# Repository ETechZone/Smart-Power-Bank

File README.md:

# Smart-Power-Bank
my current project in reewo

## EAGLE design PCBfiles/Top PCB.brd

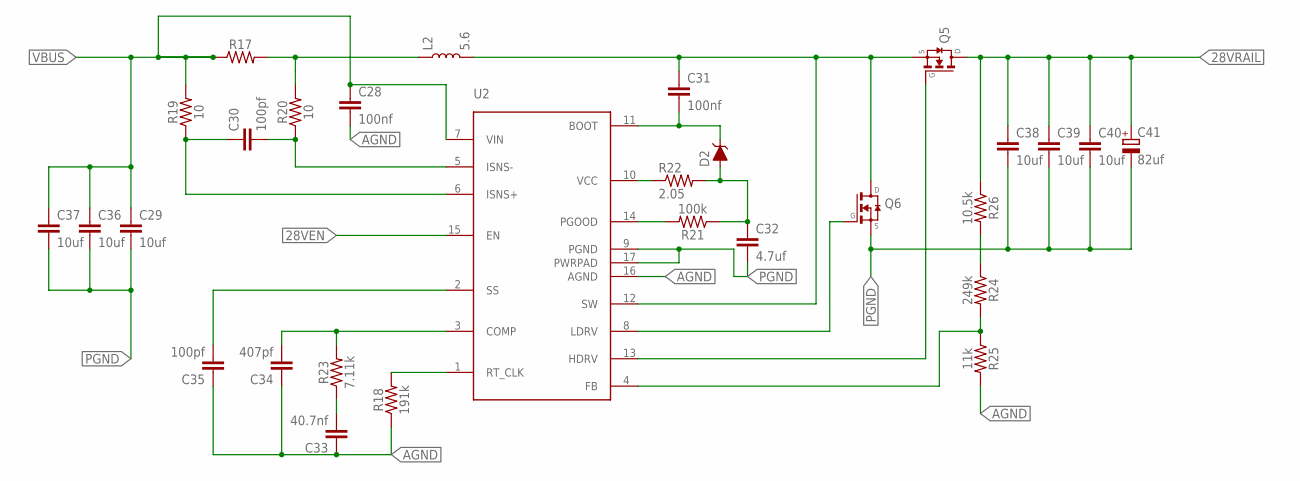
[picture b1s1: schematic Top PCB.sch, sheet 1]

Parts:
C28, C31: 100nf; C0402K
C29, C36, C37, C38, C39, C40: 10uf; C0805K
C30, C35: 100pf; C0402K
C32: 4.7uf; C0402K
C33: 40.7nf; C0402K
C34: 407pf; C0402K
C41: 82uf; CAPAE830X1040
D2: SS24FL; SODFL3617X108
L2: 5.6; RESM7275X700
Q5, Q6: SIS184DN-T1-GE3
R17: LRMAM2512-R0035FT4; RESC6432X90
R18: 191k; 0402
R19, R20: 10; 0402
R21: 100k; 0402
R22: 2.05; R0603
R23: 7.11k; 0402
R24: 249k; 0402
R25: 11k; 0402
R26: 10.5k; 0402
U2: TPS43061; QFN50P300X300X100-17T80X120

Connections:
28VEN: U2.15 (EN)
28VRAIL: C38.1, C39.1, C40.1, C41.1 (+), Q5.P$5 (D), Q5.P$6 (D), Q5.P$7 (D), Q5.P$8 (D), Q5.P$9 (D), R26.1; also elsewhere on the board
AGND: C28.2, C33.1, C34.1, C35.1, R18.1, R25.2, U2.16 (AGND)
unnamed: C31.1, L2.2, Q5.P$1 (S), Q5.P$2 (S), Q5.P$3 (S), Q6.P$5 (D), Q6.P$6 (D), Q6.P$7 (D), Q6.P$8 (D), Q6.P$9 (D), U2.12 (SW)
unnamed: R24.1, R26.2
unnamed: L2.1, R17.2, R20.2
unnamed: C30.1, R19.1, U2.6 (ISNS+)
unnamed: C30.2, R20.1, U2.5 (ISNS-)
unnamed: C31.2, D2.1 (C), U2.11 (BOOT)
unnamed: C32.1, D2.2 (A), R21.1, R22.2
unnamed: R21.2, U2.14 (PGOOD)
unnamed: R22.1, U2.10 (VCC)
unnamed: R18.2, U2.1 (RT_CLK)
unnamed: Q5.P$4 (G), U2.13 (HDRV)
unnamed: Q6.P$4 (G), U2.8 (LDRV)
unnamed: R24.2, R25.1, U2.4 (FB)
unnamed: C34.2, R23.2, U2.3 (COMP)
unnamed: C33.2, R23.1
unnamed: C35.2, U2.2 (SS)
PGND: C29.2, C32.2, C36.2, C37.2, C38.2, C39.2, C40.2, C41.2 (-), Q6.P$1 (S), Q6.P$2 (S), Q6.P$3 (S), U2.9 (PGND), U2.17 (PWRPAD); also elsewhere on the board
VBUS: C28.1, C29.1, C36.1, C37.1, R17.1, R19.2, U2.7 (VIN)

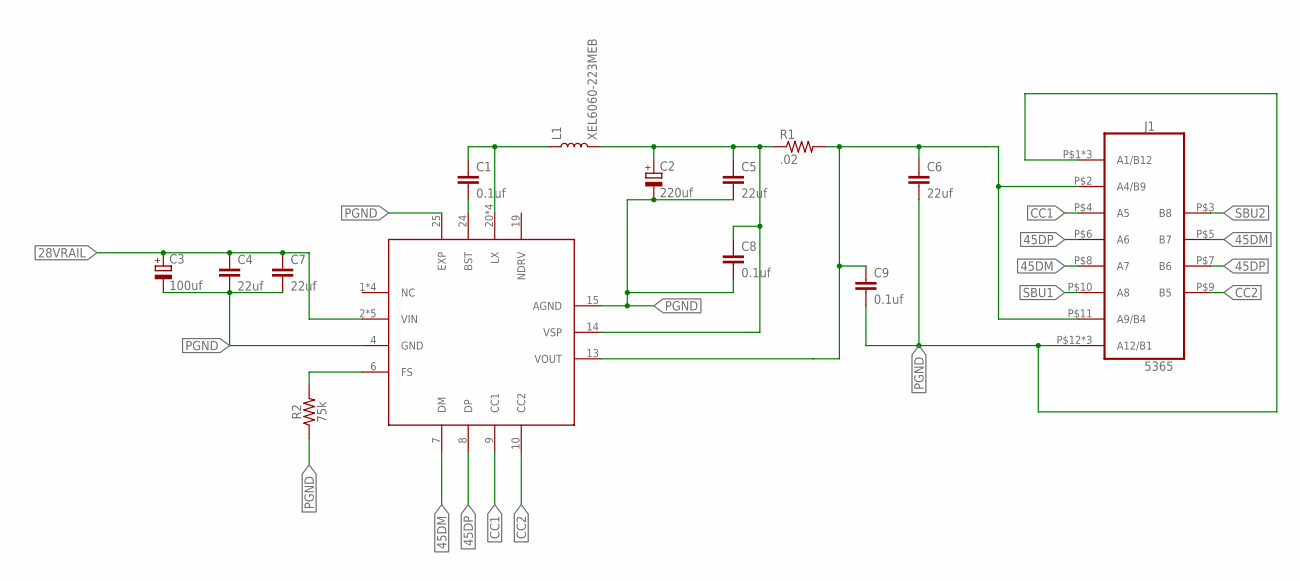
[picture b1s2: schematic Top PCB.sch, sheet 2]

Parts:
C1, C8, C9: 0.1uf; C0805K
C2: 220uf; CAPAE830X1040
C3: 100uf; CAPAE830X1040
C4, C5, C6, C7: 22uf; C0805K
J1: 5365
L1: XEL6060-223MEB; RESM6365X610
R1: .02; R0805
R2: 75k; 0402
U1: IP6518; QFN50P400X400X80-25T250

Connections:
28VRAIL: C3.1 (+), C4.1, C7.1, U1.2 (VIN), U1.3 (VIN), U1.16 (VIN), U1.17 (VIN), U1.18 (VIN); also elsewhere on the board
45DM: J1.P$5 (B7), J1.P$8 (A7), U1.7 (DM)
45DP: J1.P$6 (A6), J1.P$7 (B6), U1.8 (DP)
CC1: J1.P$4 (A5), U1.9 (CC1)
CC2: J1.P$9 (B5), U1.10 (CC2)
unnamed: C1.1, L1.1, U1.20 (LX), U1.21 (LX), U1.22 (LX), U1.23 (LX)
unnamed: C1.2, U1.24 (BST)
unnamed: C2.1 (+), C5.1, C8.1, L1.2, R1.1, U1.14 (VSP)
unnamed: C6.1, C9.1, J1.P$2 (A4/B9), J1.P$11 (A9/B4), R1.2, U1.13 (VOUT)
unnamed: R2.2, U1.6 (FS)
PGND: C2.2 (-), C3.2 (-), C4.2, C5.2, C6.2, C7.2, C8.2, C9.2, J1.P$1 (A1/B12), J1.P$12 (A12/B1), J1.P$13 (A1/B12), J1.P$14 (A12/B1), J1.P$15 (A1/B12), J1.P$16 (A12/B1), R2.1, U1.4 (GND), U1.15 (AGND), U1.25 (EXP); also elsewhere on the board
SBU1: J1.P$10 (A8)
SBU2: J1.P$3 (B8)

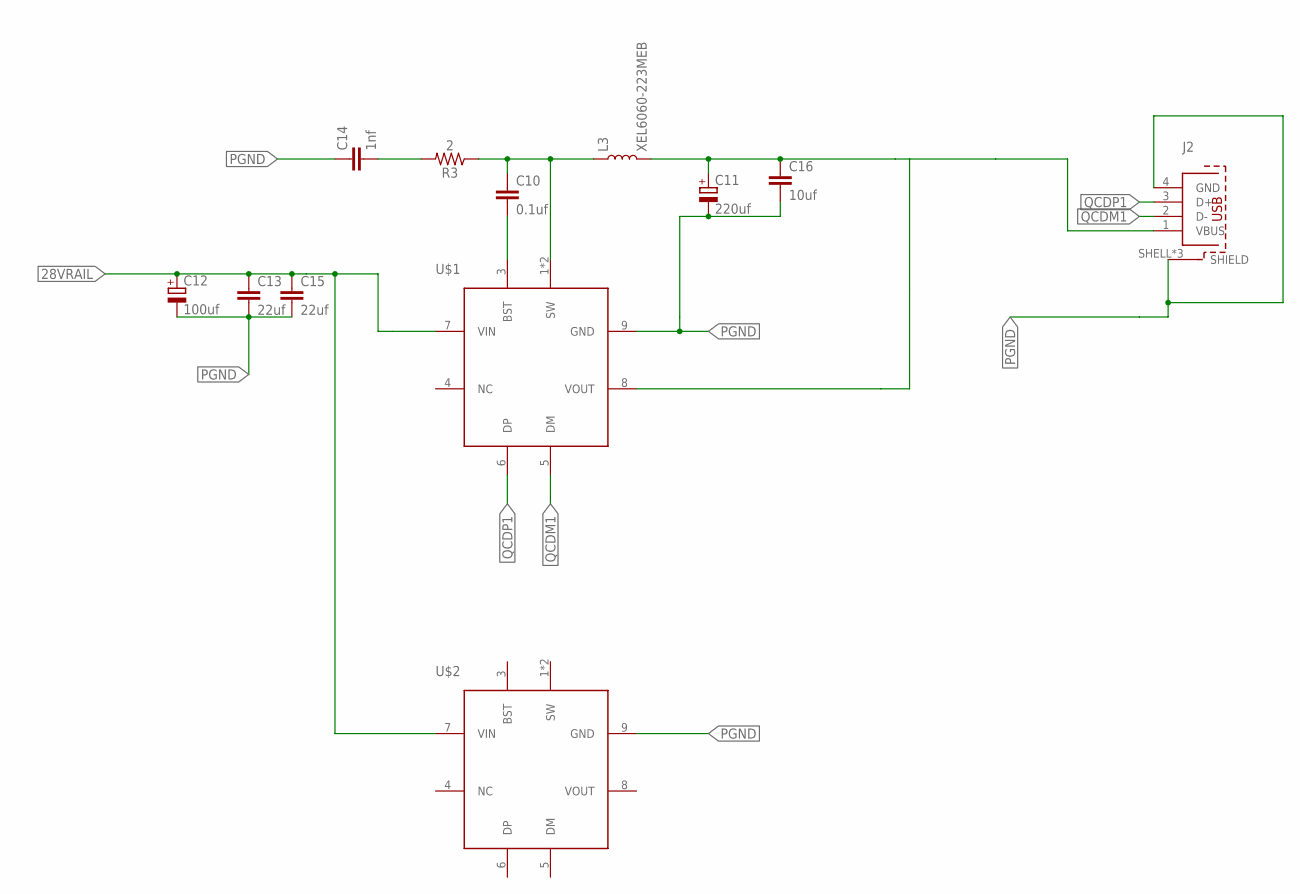
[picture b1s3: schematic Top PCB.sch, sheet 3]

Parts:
C10: 0.1uf; C0805K
C11: 220uf; CAPAE830X1040
C12: 100uf; CAPAE830X1040
C13, C15: 22uf; C0805K
C14: 1nf; C0402K
C16: 10uf; C0805K
J2: 614004184726
L3: XEL6060-223MEB; RESM6365X610
R3: 2; 0402
U$1, U$2: IP6505; SOIC127P600X165-9T209

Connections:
28VRAIL: C12.1 (+), C13.1, C15.1, U$1.7 (VIN), U$2.7 (VIN); also elsewhere on the board
unnamed: C10.1, L3.1, R3.1, U$1.1 (SW), U$1.2 (SW)
unnamed: C10.2, U$1.3 (BST)
unnamed: C14.2, R3.2
unnamed: J2.1 (VBUS), U$1.8 (VOUT)
unnamed: C11.1 (+), C16.1, L3.2
PGND: C11.2 (-), C12.2 (-), C13.2, C14.1, C15.2, C16.2, J2.4 (GND), J2.SHELL (SHIELD), J2.SHELL1 (SHIELD), J2.SHELL2 (SHIELD), U$1.9 (GND), U$2.9 (GND); also elsewhere on the board
QCDM1: J2.2 (D-), U$1.5 (DM)
QCDP1: J2.3 (D+), U$1.6 (DP)

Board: 2 copper layers, 55 parts (0 on the bottom side), 36 nets, no tracks yet.

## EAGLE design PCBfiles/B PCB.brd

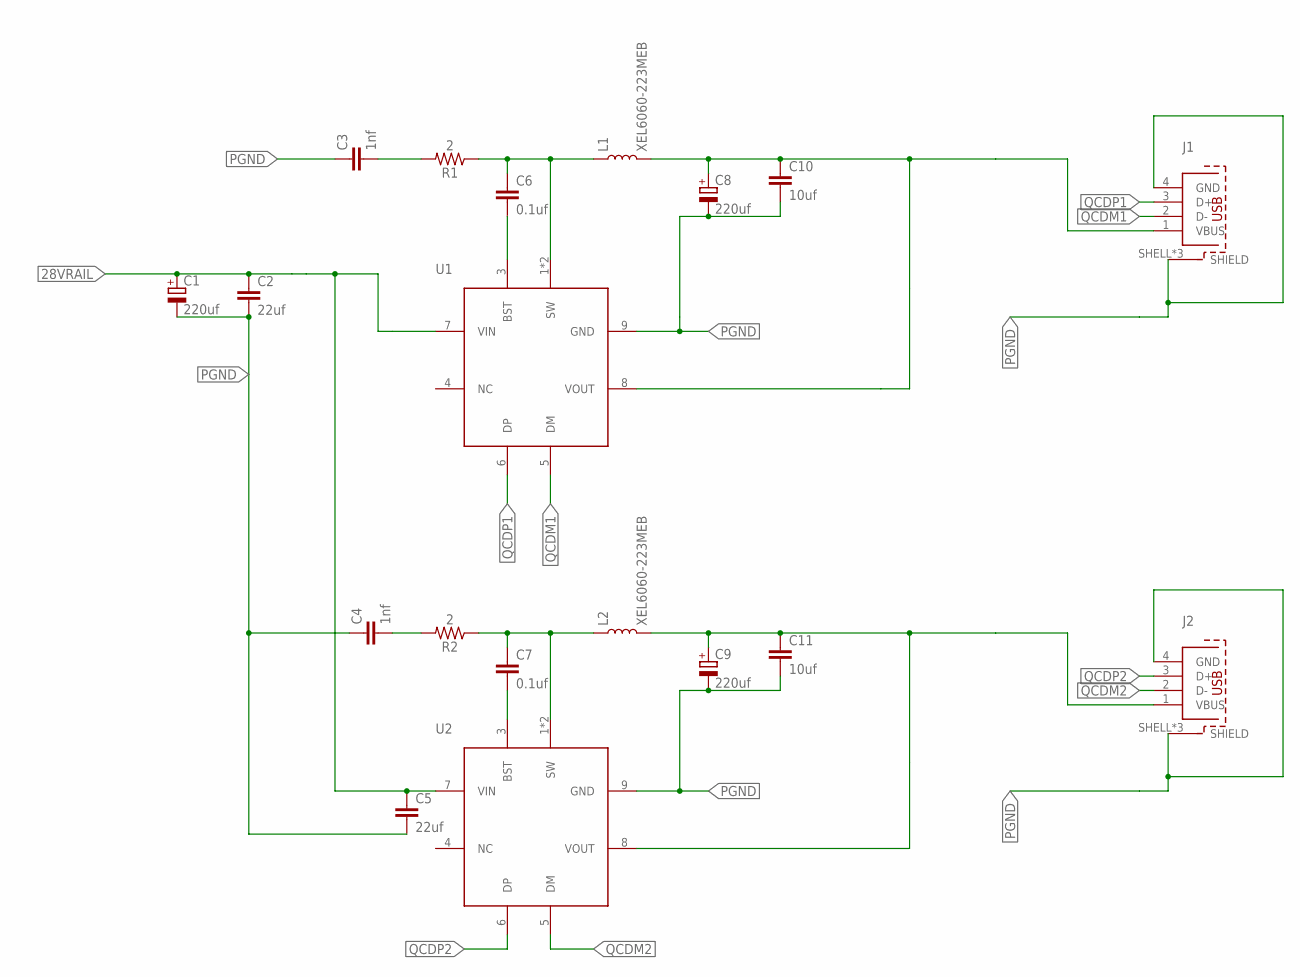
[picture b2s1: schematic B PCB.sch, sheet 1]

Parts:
C1: 220uf; CAPAE830X1040
C2, C5: 22uf; C0805K
C3, C4: 1nf; C0402K
C6, C7: 0.1uf; C0805K
C8, C9: 220uf; CAPAE660X800
C10, C11: 10uf; C0805K
J1, J2: 614004184726
L1, L2: XEL6060-223MEB; RESM6365X610
R1, R2: 2; 0402
U1, U2: IP6505; SOIC127P600X165-9T209

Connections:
28VRAIL: C1.1 (+), C2.1, C5.1, U1.7 (VIN), U2.7 (VIN); also elsewhere on the board
unnamed: C7.1, L2.1, R2.1, U2.1 (SW), U2.2 (SW)
unnamed: C7.2, U2.3 (BST)
unnamed: C6.1, L1.1, R1.1, U1.1 (SW), U1.2 (SW)
unnamed: C9.1 (+), C11.1, J2.1 (VBUS), L2.2, U2.8 (VOUT)
unnamed: C4.2, R2.2
unnamed: C6.2, U1.3 (BST)
unnamed: C3.2, R1.2
unnamed: C8.1 (+), C10.1, J1.1 (VBUS), L1.2, U1.8 (VOUT)
PGND: C1.2 (-), C2.2, C3.1, C4.1, C5.2, C8.2 (-), C9.2 (-), C10.2, C11.2, J1.4 (GND), J1.SHELL (SHIELD), J1.SHELL1 (SHIELD), J1.SHELL2 (SHIELD), J2.4 (GND), J2.SHELL (SHIELD), J2.SHELL1 (SHIELD), J2.SHELL2 (SHIELD), U1.9 (GND), U2.9 (GND); also elsewhere on the board
QCDM1: J1.2 (D-), U1.5 (DM)
QCDM2: J2.2 (D-), U2.5 (DM)
QCDP1: J1.3 (D+), U1.6 (DP)
QCDP2: J2.3 (D+), U2.6 (DP)

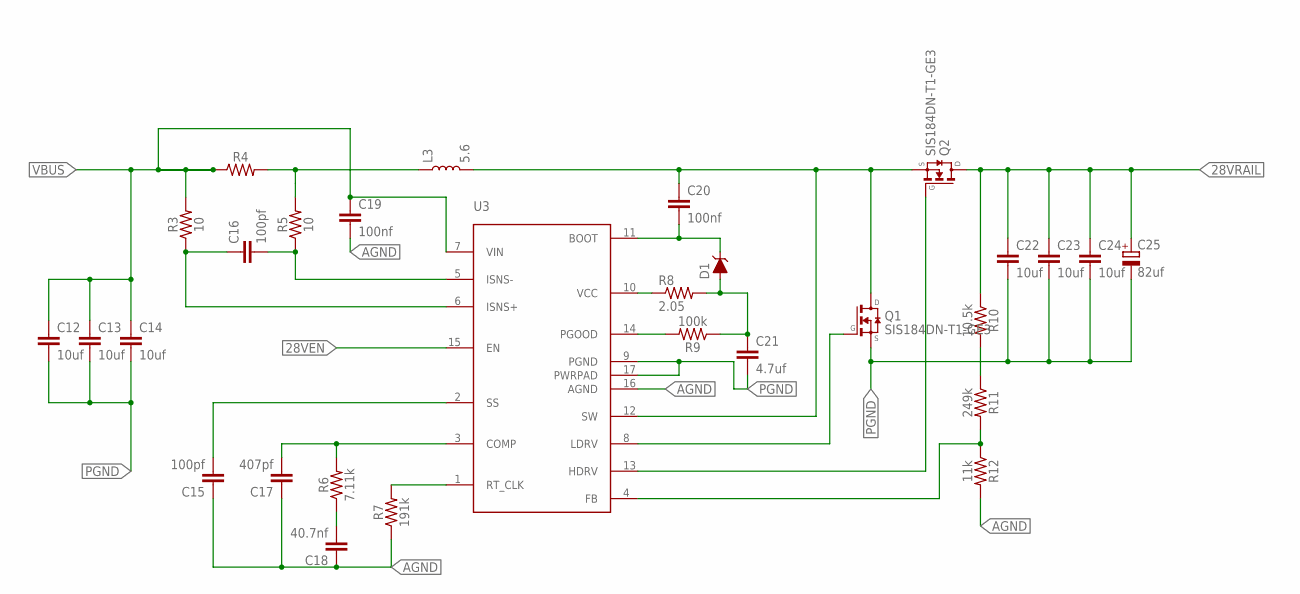
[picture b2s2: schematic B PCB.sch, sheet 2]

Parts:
C12, C13, C14, C22, C23, C24: 10uf; C0805K
C15, C16: 100pf; C0402K
C17: 407pf; C0402K
C18: 40.7nf; C0402K
C19, C20: 100nf; C0402K
C21: 4.7uf; C0402K
C25: 82uf; CAPAE660X800
D1: SS24FL; SODFL3617X108
L3: 5.6; RESM7275X700
Q1, Q2: SIS184DN-T1-GE3
R3, R5: 10; 0402
R4: LRMAM2512-R0035FT4; RESC6432X90
R6: 7.11k; 0402
R7: 191k; 0402
R8: 2.05; R0603
R9: 100k; 0402
R10: 10.5k; 0402
R11: 249k; 0402
R12: 11k; 0402
U3: TPS43061; QFN50P300X300X100-17T80X120

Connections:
28VEN: U3.15 (EN)
28VRAIL: C22.1, C23.1, C24.1, C25.1 (+), Q2.P$5 (D), Q2.P$6 (D), Q2.P$7 (D), Q2.P$8 (D), Q2.P$9 (D), R10.1; also elsewhere on the board
AGND: C15.1, C17.1, C18.1, C19.2, R7.1, R12.2, U3.16 (AGND)
unnamed: C20.1, L3.2, Q1.P$5 (D), Q1.P$6 (D), Q1.P$7 (D), Q1.P$8 (D), Q1.P$9 (D), Q2.P$1 (S), Q2.P$2 (S), Q2.P$3 (S), U3.12 (SW)
unnamed: R10.2, R11.1
unnamed: L3.1, R4.2, R5.2
unnamed: C16.1, R3.1, U3.6 (ISNS+)
unnamed: C16.2, R5.1, U3.5 (ISNS-)
unnamed: C20.2, D1.1 (C), U3.11 (BOOT)
unnamed: C21.1, D1.2 (A), R8.2, R9.1
unnamed: R9.2, U3.14 (PGOOD)
unnamed: R8.1, U3.10 (VCC)
unnamed: R7.2, U3.1 (RT_CLK)
unnamed: Q2.P$4 (G), U3.13 (HDRV)
unnamed: Q1.P$4 (G), U3.8 (LDRV)
unnamed: R11.2, R12.1, U3.4 (FB)
unnamed: C17.2, R6.2, U3.3 (COMP)
unnamed: C18.2, R6.1
unnamed: C15.2, U3.2 (SS)
PGND: C12.2, C13.2, C14.2, C21.2, C22.2, C23.2, C24.2, C25.2 (-), Q1.P$1 (S), Q1.P$2 (S), Q1.P$3 (S), U3.9 (PGND), U3.17 (PWRPAD); also elsewhere on the board
VBUS: C12.1, C13.1, C14.1, C19.1, R3.2, R4.1, U3.7 (VIN)

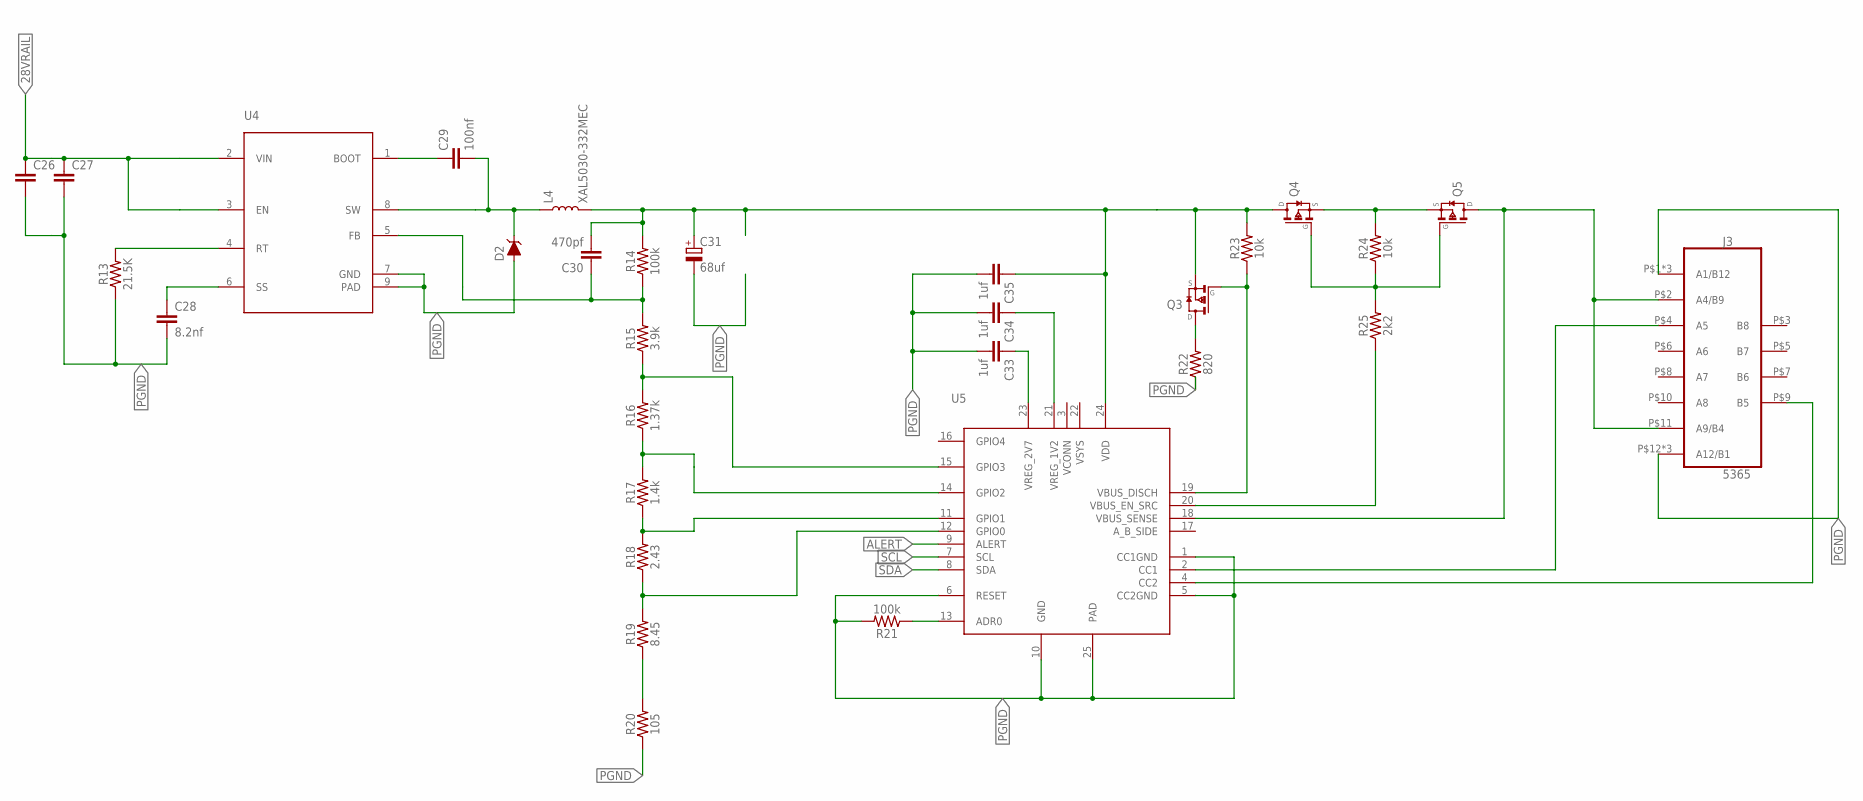
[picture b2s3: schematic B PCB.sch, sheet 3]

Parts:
C26, C27: C-EUC1210; C1210
C28: 8.2nf; C0402K
C29: 100nf; C0402K
C30: 470pf; C0402K
C31: 68uf; CAPAE830X1040
C33, C34, C35: 1uf; C0402K
D2: B560C-13-F; DIOM6859X250
J3: 5365
L4: XAL5030-332MEC; INDM5355X310
Q3: STR2P3LLH6; SOT95P280X125-3
Q4, Q5: STL9P3LLH6; SON65P330X330X80-8
R13: 21.5K; 0402
R14, R21: 100k; 0402
R15: 3.9k; 0402
R16: 1.37k; 0402
R17: 1.4k; 0402
R18: 2.43; 0402
R19: 8.45; 0402
R20: 105; 0402
R22: 820; 0402
R23, R24: 10k; 0402
R25: 2k2; 0402
U4: LMR14050; SOIC127P600X170-9T240X260
U5: STUSB4700; QFN50P400X400X100-25T270

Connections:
28VRAIL: C26.1, C27.1, U4.2 (VIN), U4.3 (EN); also elsewhere on the board
ALERT: U5.9 (ALERT)
unnamed: C33.1, U5.23 (VREG_2V7)
unnamed: C34.1, U5.21 (VREG_1V2)
unnamed: Q3.3 (D), R22.2
unnamed: C30.1, R14.1, R15.2, U4.5 (FB)
unnamed: R15.1, R16.2, U5.15 (GPIO3)
unnamed: R16.1, R17.2, U5.14 (GPIO2)
unnamed: R17.1, R18.2, U5.11 (GPIO1)
unnamed: R18.1, R19.2, U5.12 (GPIO0)
unnamed: R19.1, R20.2
unnamed: R21.1, U5.13 (ADR0)
unnamed: C29.1, U4.1 (BOOT)
unnamed: C29.2, D2.1 (C), L4.1, U4.8 (SW)
unnamed: C28.1, U4.6 (SS)
unnamed: Q4.1 (S), Q4.2 (S), Q4.3 (S), Q5.1 (S), Q5.2 (S), Q5.3 (S), R24.2
unnamed: R13.2, U4.4 (RT)
unnamed: C30.2, C31.1 (+), C35.1, L4.2, Q3.2 (S), Q4.5 (D), Q4.6 (D), Q4.7 (D), R14.2, R23.2, U5.24 (VDD)
unnamed: Q3.1 (G), R23.1, U5.19 (VBUS_DISCH)
unnamed: Q4.4 (G), Q5.4 (G), R24.1, R25.2
unnamed: R25.1, U5.20 (VBUS_EN_SRC)
unnamed: J3.P$2 (A4/B9), J3.P$11 (A9/B4), Q5.5 (D), Q5.6 (D), Q5.7 (D), U5.18 (VBUS_SENSE)
unnamed: J3.P$4 (A5), U5.2 (CC1)
unnamed: J3.P$9 (B5), U5.4 (CC2)
PGND: C26.2, C27.2, C28.2, C31.2 (-), C33.2, C34.2, C35.2, D2.2 (A), J3.P$1 (A1/B12), J3.P$12 (A12/B1), J3.P$13 (A1/B12), J3.P$14 (A12/B1), J3.P$15 (A1/B12), J3.P$16 (A12/B1), R13.1, R20.1, R21.2, R22.1, U4.7 (GND), U4.9 (PAD), U5.1 (CC1GND), U5.5 (CC2GND), U5.6 (RESET), U5.10 (GND), U5.25 (PAD); also elsewhere on the board
SCL: U5.7 (SCL)
SDA: U5.8 (SDA)

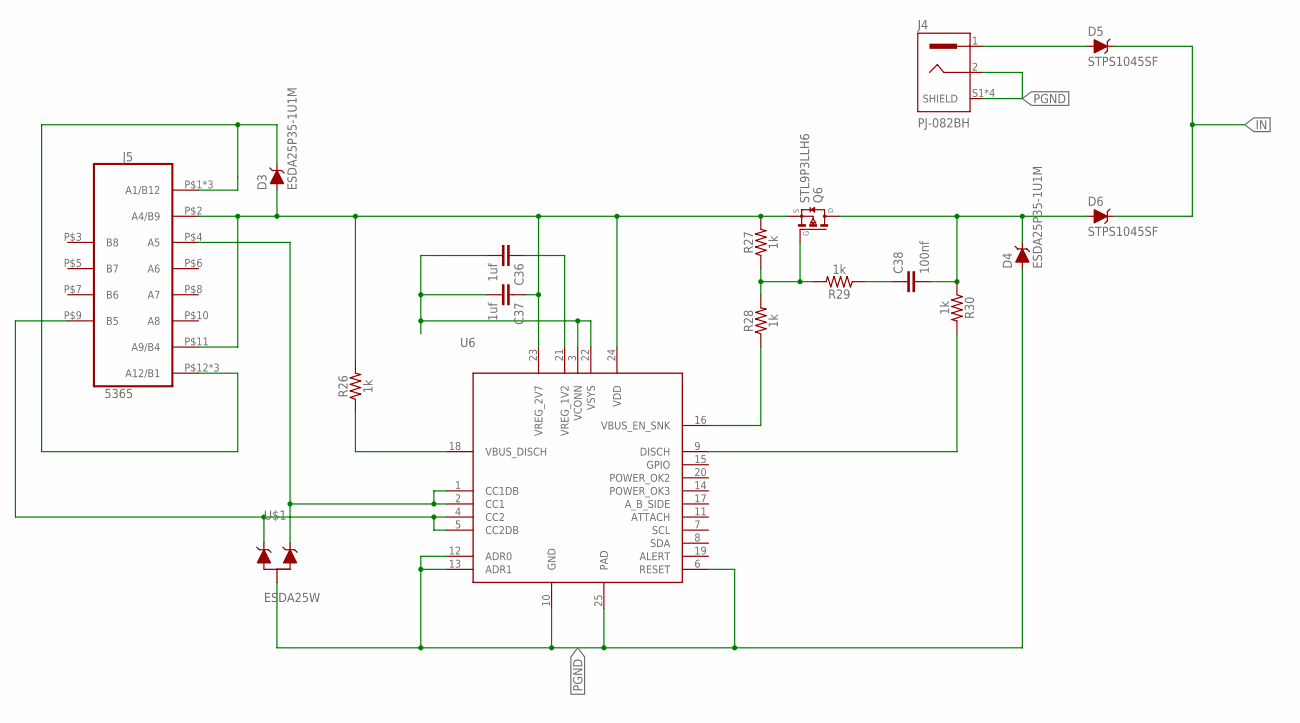
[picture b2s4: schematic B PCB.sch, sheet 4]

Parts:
C36, C37: 1uf; C0402K
C38: 100nf; C0402K
D3, D4: ESDA25P35-1U1M; DIODFN160X100X60-2
D5, D6: STPS1045SF; DIODFN650X460X120-3
J4: PJ-082BH; CUI_PJ-082BH
J5: 5365
Q6: STL9P3LLH6; SON65P330X330X80-8
R26, R27, R28, R29, R30: 1k; 0402
U6: STUSB4500; QFN50P400X400X100-25T270
U$1: ESDA25W; SOT65P210X110-3

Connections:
IN: D5.3 (C), D6.3 (C)
unnamed: D5.1 (A), D5.2 (A), J4.1
unnamed: D3.1 (C), J5.P$1 (A1/B12), J5.P$12 (A12/B1), J5.P$13 (A1/B12), J5.P$14 (A12/B1), J5.P$15 (A1/B12), J5.P$16 (A12/B1)
unnamed: J5.P$4 (A5), U6.1 (CC1DB), U6.2 (CC1), U$1.2 (C2)
unnamed: J5.P$9 (B5), U6.4 (CC2), U6.5 (CC2DB), U$1.1 (C1)
unnamed: R26.1, U6.18 (VBUS_DISCH)
unnamed: C36.1, U6.21 (VREG_1V2)
unnamed: C36.2, C37.2, U6.3 (VCONN), U6.22 (VSYS)
unnamed: C37.1, D3.2 (A), J5.P$2 (A4/B9), J5.P$11 (A9/B4), Q6.1 (S), Q6.2 (S), Q6.3 (S), R26.2, R27.2, U6.23 (VREG_2V7), U6.24 (VDD)
unnamed: Q6.4 (G), R27.1, R28.2, R29.2
unnamed: R28.1, U6.16 (VBUS_EN_SNK)
unnamed: R30.2, U6.9 (DISCH)
unnamed: C38.1, R29.1
unnamed: C38.2, D4.1 (C), D6.1 (A), D6.2 (A), Q6.5 (D), Q6.6 (D), Q6.7 (D), R30.1
PGND: D4.2 (A), J4.2, J4.S1 (SHIELD), J4.S2 (SHIELD), J4.S3 (SHIELD), J4.S4 (SHIELD), U6.6 (RESET), U6.10 (GND), U6.12 (ADR0), U6.13 (ADR1), U6.25 (PAD), U$1.3 (A); also elsewhere on the board

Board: 4 copper layers, 95 parts (0 on the bottom side), 68 nets, no tracks yet.

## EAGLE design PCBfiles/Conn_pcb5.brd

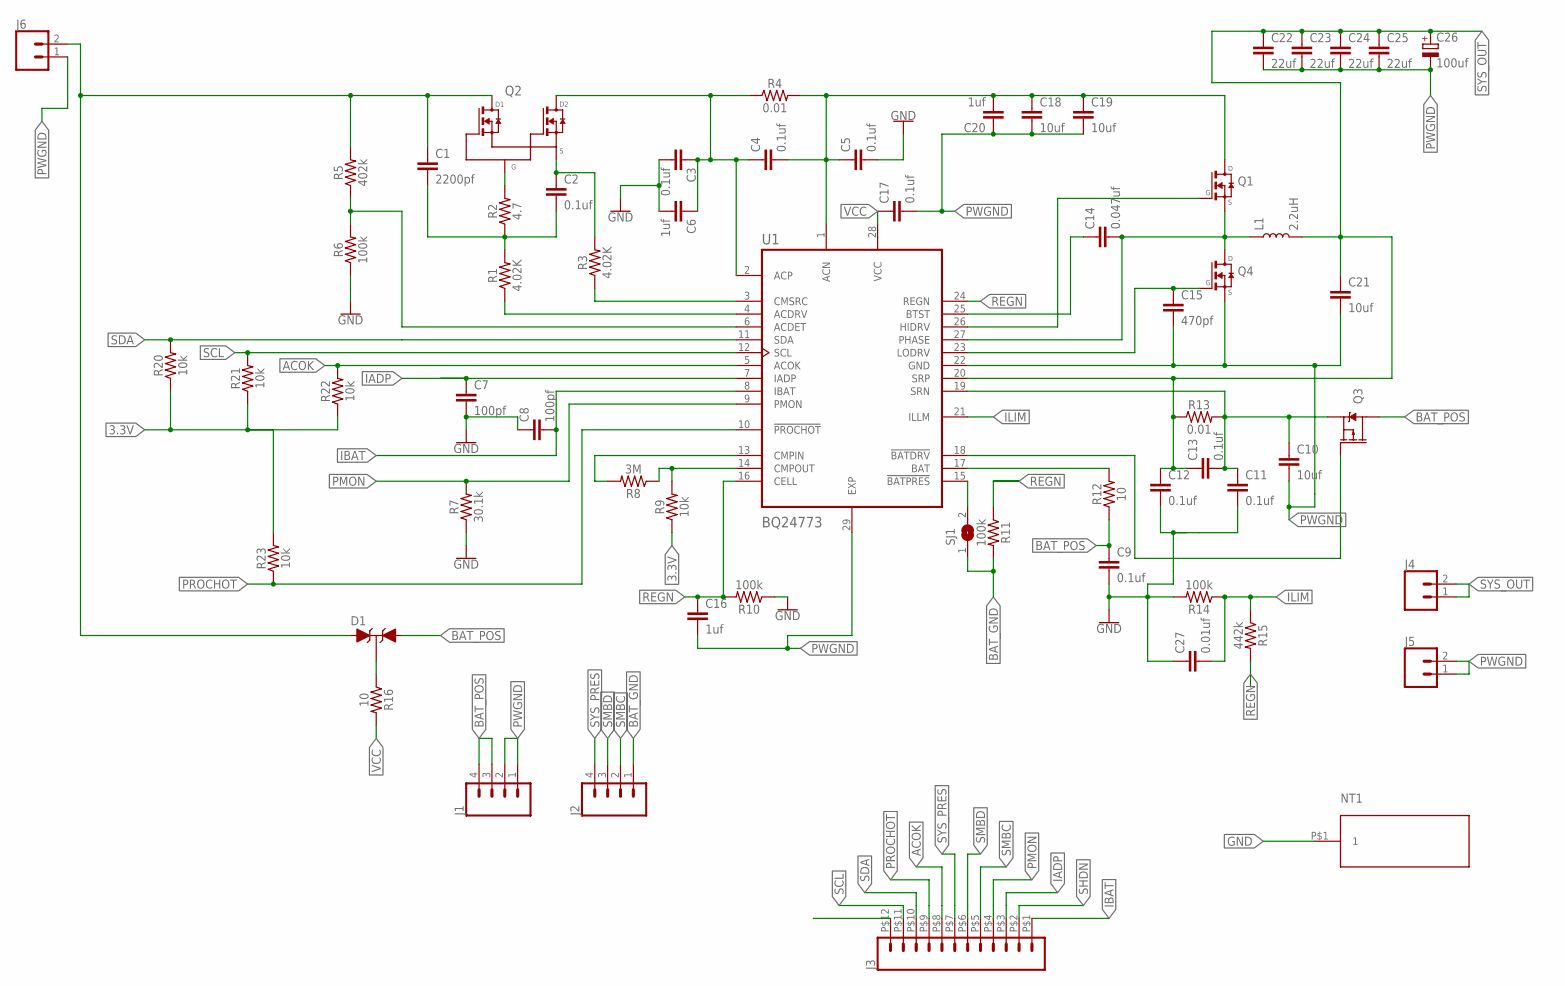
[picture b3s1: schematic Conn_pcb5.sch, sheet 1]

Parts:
C1: 2200pf; CAPC1005X50
C2, C3, C4, C5, C9, C11, C12, C13, C17: 0.1uf; CAPC1005X50
C6, C16, C20: 1uf; CAPC1005X50
C7, C8: 100pf; CAPC1005X50
C10, C18, C19, C21: 10uf; C0805K
C14: 0.047uf; CAPC1005X50
C15: 470pf; CAPC1005X50
C22, C23, C24, C25: 22uf; C1206
C26: 100uf; CAPAE1030X800
C27: 0.01uf; CAPC1005X50
D1: BAT54C-7-F; SOT95P235X110-3
J1, J2: CONN_041.3; 1X04_NO_SILK_1.3
J3: 62674-121121ALF
J4, J5, J6: CONN_021.4HOLE; 1X02_1.4HOLE
L1: 2.2uH; RESM6365X610
NT1: NET_TIE
Q1, Q4: CSD17308Q3; SON65P330X330X110-8
Q2: CSD87312Q3EVSON; QFN65P330X330X100-12
Q3: CSD25402Q3A
R1, R3: 4.02K; 0402
R2: 4.7; 0402
R4, R13: 0.01; 1206
R5: 402k; 0402
R6, R10, R11, R14: 100k; 0402
R7: 30.1k; 0402
R8: 3M; 0402
R9, R20, R21, R22, R23: 10k; 0402
R12, R16: 10; 0402
R15: 442k; 0402
SJ1: SJ
U1: BQ24773; QFN40P400X400X80-29T240

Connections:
3.3V: R9.1, R20.1, R21.1, R22.1, R23.2; also elsewhere on the board
ACOK: J3.P$8 (8), R22.2, U1.5 (ACOK)
BAT_GND: J2.1, R11.2, SJ1.1
BAT_POS: C9.1, D1.2 (A2), J1.3, J1.4, Q3.1 (D), Q3.2 (D), Q3.3 (D), R12.1; also elsewhere on the board
GND: C3.2, C5.2, C6.2, C7.2, C8.1, C9.2, C11.2, C12.2, C27.1, NT1.P$1, R6.1, R7.1, R10.1, R14.2
IADP: C7.1, J3.P$3 (3), U1.7 (IADP)
IBAT: C8.2, J3.P$1 (1), U1.8 (IBAT)
ILIM: C27.2, R14.1, R15.1, U1.21 (ILLM)
unnamed: R1.1, U1.4 (ACDRV)
unnamed: C1.2, C2.2, R1.2, R2.1
unnamed: Q2.5 (G), R2.2
unnamed: C1.1, D1.1 (A1), J6.2, Q2.1 (D1), Q2.3 (D1), Q2.4 (D1), R5.2
unnamed: R5.1, R6.2, U1.6 (ACDET)
unnamed: C4.2, C5.1, C18.1, C19.1, C20.2, Q1.5 (D), Q1.6 (D), Q1.7 (D), Q1.8 (D), R4.2, U1.1 (ACN)
unnamed: C2.1, Q2.9 (S), Q2.9.1 (S), Q2.9.2 (S), Q2.9.3 (S), Q2.9.4 (S), R3.2
unnamed: R3.1, U1.3 (CMSRC)
unnamed: C3.1, C4.1, C6.1, Q2.6 (D2), Q2.7 (D2), Q2.8 (D2), R4.1, U1.2 (ACP)
unnamed: R8.2, U1.13 (CMPIN)
unnamed: R8.1, R9.2, U1.14 (CMPOUT)
unnamed: R12.2, U1.17 (BAT)
unnamed: Q3.4 (G), U1.18 (!BATDRV)
unnamed: C10.1, C11.1, C13.2, Q3.5 (S), Q3.6 (S), Q3.7 (S), Q3.8 (S), Q3.9 (S), R13.2, U1.19 (SRN)
unnamed: C15.1, Q4.4 (G), U1.23 (LODRV)
unnamed: SJ1.2, U1.15 (!BATPRES)
unnamed: D1.3 (K), R16.1
unnamed: C14.2, L1.1, Q1.1 (S), Q1.2 (S), Q1.3 (S), Q4.5 (D), Q4.6 (D), Q4.7 (D), Q4.8 (D), U1.27 (PHASE)
unnamed: C14.1, U1.25 (BTST)
unnamed: Q1.4 (G), U1.26 (HIDRV)
PMON: J3.P$4 (4), R7.2, U1.9 (PMON)
PROCHOT: J3.P$9 (9), R23.1, U1.10 (!PROCHOT)
PWGND: C10.2, C15.2, C16.2, C17.2, C18.2, C19.2, C20.1, C21.2, C22.2, C23.2, C24.2, C25.2, C26.2 (-), J1.1, J1.2, J5.1, J5.2, J6.1, Q4.1 (S), Q4.2 (S), Q4.3 (S), U1.22 (GND), U1.29 (EXP); also elsewhere on the board
REGN: C16.1, R10.2, R11.1, R15.2, U1.16 (CELL), U1.24 (REGN)
SCL: J3.P$11 (11), R21.2, U1.12 (SCL)
SDA: J3.P$10 (10), R20.2, U1.11 (SDA)
SHDN: J3.P$2 (2); also elsewhere on the board
SMBC: J2.2, J3.P$5 (5)
SMBD: J2.3, J3.P$6 (6)
SYS_OUT: C12.1, C13.1, C21.1, C22.1, C23.1, C24.1, C25.1, C26.1 (+), J4.1, J4.2, L1.2, R13.1, U1.20 (SRP); also elsewhere on the board
SYS_PRES: J2.4, J3.P$7 (7)
VCC: C17.1, R16.2, U1.28 (VCC)

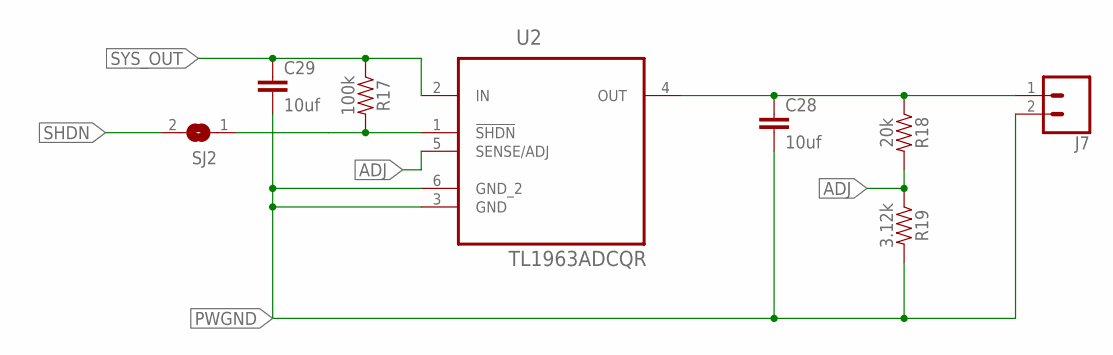
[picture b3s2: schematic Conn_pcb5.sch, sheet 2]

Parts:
C28, C29: 10uf; C0805K
J7: CONN_02; 1X02
R17: 100k; 0402
R18: 20k; 0402
R19: 3.12k; 0402
SJ2: SJ
U2: TL1963ADCQR; SOT127P706X180-6

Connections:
ADJ: R18.2, R19.1, U2.5 (SENSE/ADJ)
unnamed: C28.1, J7.1, R18.1, U2.4 (OUT)
unnamed: R17.2, SJ2.1, U2.1 (!SHDN)
PWGND: C28.2, C29.2, J7.2, R19.2, U2.3 (GND), U2.6 (GND_2); also elsewhere on the board
SHDN: SJ2.2; also elsewhere on the board
SYS_OUT: C29.1, R17.1, U2.2 (IN); also elsewhere on the board

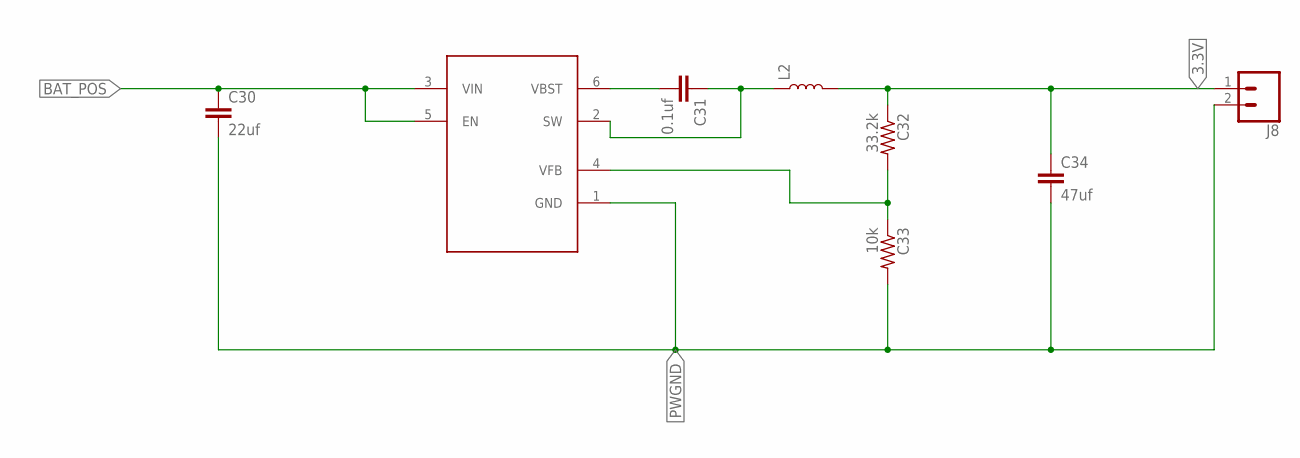
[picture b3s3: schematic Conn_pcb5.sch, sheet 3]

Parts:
C30: 22uf; C1206
C31: 0.1uf; CAPC1005X50
C32: 33.2k; R0805
C33: 10k; R0603
C34: 47uf; C1206K
J8: CONN_02; 1X02
L2: ASPI-4030S-3R3M-T; INDDFN400X400X300-2
U3: TPS561208DDCR; SOT95P280X110-6

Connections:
3.3V: C32.1, C34.1, J8.1, L2.2; also elsewhere on the board
BAT_POS: C30.1, U3.3 (VIN), U3.5 (EN); also elsewhere on the board
unnamed: C31.2, U3.6 (VBST)
unnamed: C31.1, L2.1, U3.2 (SW)
unnamed: C32.2, C33.1, U3.4 (VFB)
PWGND: C30.2, C33.2, C34.2, J8.2, U3.1 (GND); also elsewhere on the board

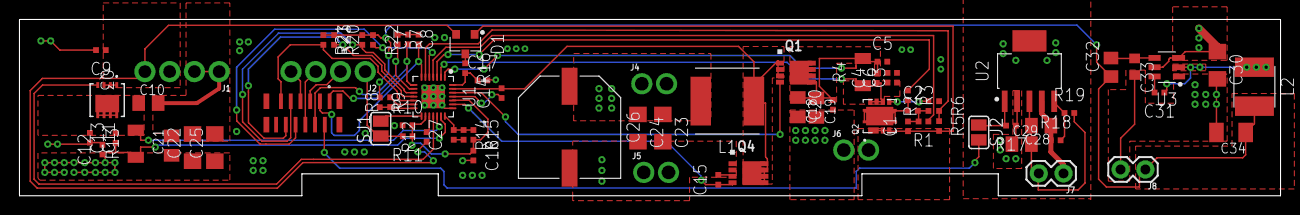
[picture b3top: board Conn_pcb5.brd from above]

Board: 4 copper layers, 129.5 x 18.1 mm, 78 parts (1 on the bottom side), 46 nets.

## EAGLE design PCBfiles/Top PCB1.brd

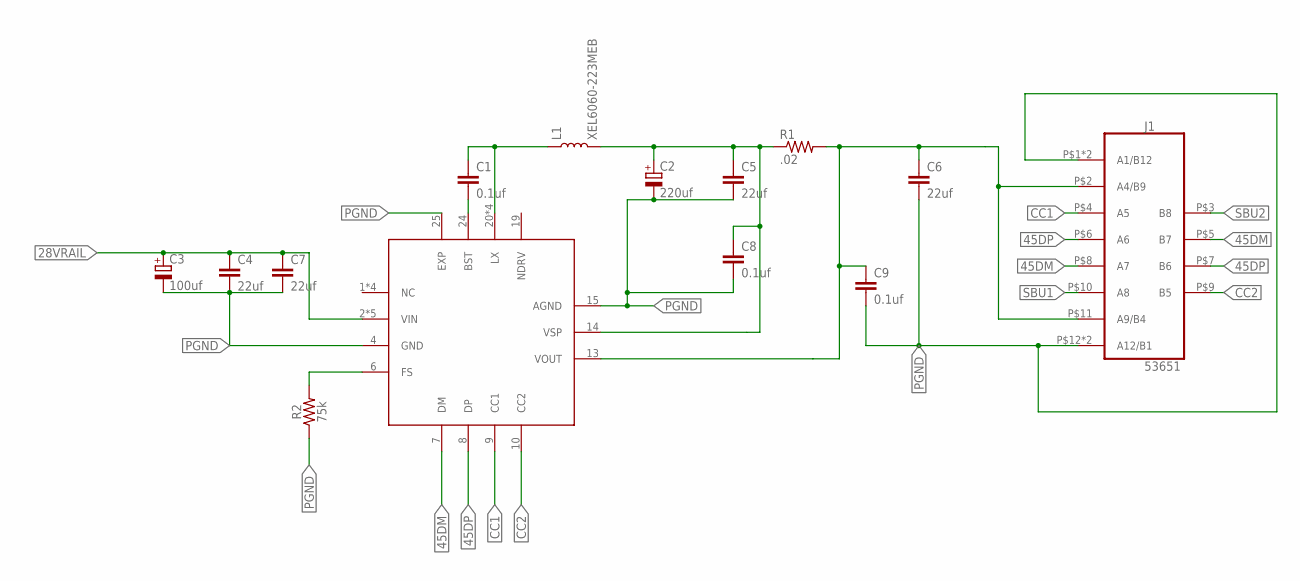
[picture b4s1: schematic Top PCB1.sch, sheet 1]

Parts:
C1, C8, C9: 0.1uf; C0805K
C2: 220uf; CAPAE660X800
C3: 100uf; CAPAE660X800
C4, C5, C6, C7: 22uf; C0805K
J1: 53651
L1: XEL6060-223MEB; RESM6365X610
R1: .02; R0805
R2: 75k; 0402
U1: IP6518; QFN50P400X400X80-25T250

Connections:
28VRAIL: C3.1 (+), C4.1, C7.1, U1.2 (VIN), U1.3 (VIN), U1.16 (VIN), U1.17 (VIN), U1.18 (VIN)
45DM: J1.P$5 (B7), J1.P$8 (A7), U1.7 (DM)
45DP: J1.P$6 (A6), J1.P$7 (B6), U1.8 (DP)
CC1: J1.P$4 (A5), U1.9 (CC1)
CC2: J1.P$9 (B5), U1.10 (CC2)
unnamed: C1.1, L1.1, U1.20 (LX), U1.21 (LX), U1.22 (LX), U1.23 (LX)
unnamed: C1.2, U1.24 (BST)
unnamed: C2.1 (+), C5.1, C8.1, L1.2, R1.1, U1.14 (VSP)
unnamed: C6.1, C9.1, J1.P$2 (A4/B9), J1.P$11 (A9/B4), R1.2, U1.13 (VOUT)
unnamed: R2.2, U1.6 (FS)
PGND: C2.2 (-), C3.2 (-), C4.2, C5.2, C6.2, C7.2, C8.2, C9.2, J1.P$1 (A1/B12), J1.P$12 (A12/B1), J1.P$13 (A1/B12), J1.P$14 (A12/B1), R2.1, U1.4 (GND), U1.15 (AGND), U1.25 (EXP)
SBU1: J1.P$10 (A8)
SBU2: J1.P$3 (B8)

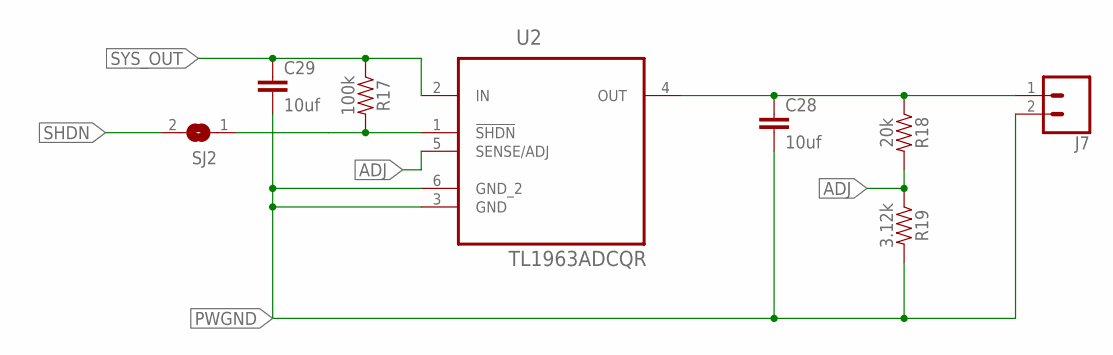
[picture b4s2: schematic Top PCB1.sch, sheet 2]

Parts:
C28, C29: 10uf; C0805K
J7: CONN_02; 1X02
R17: 100k; 0402
R18: 20k; 0402
R19: 3.12k; 0402
SJ2: SJ
U2: TL1963ADCQR; SOT127P706X180-6

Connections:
ADJ: R18.2, R19.1, U2.5 (SENSE/ADJ)
unnamed: C28.1, J7.1, R18.1, U2.4 (OUT)
unnamed: R17.2, SJ2.1, U2.1 (!SHDN)
PWGND: C28.2, C29.2, J7.2, R19.2, U2.3 (GND), U2.6 (GND_2); also elsewhere on the board
SHDN: SJ2.2
SYS_OUT: C29.1, R17.1, U2.2 (IN)

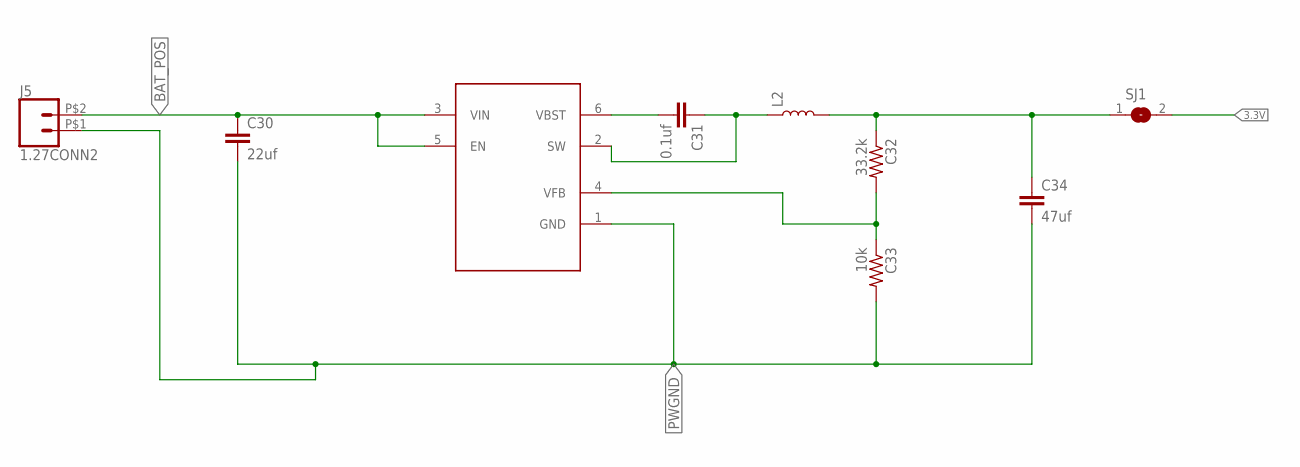
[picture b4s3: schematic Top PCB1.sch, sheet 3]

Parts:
C30: 22uf; C1206
C31: 0.1uf; CAPC1005X50
C32: 33.2k; R0805
C33: 10k; R0603
C34: 47uf; C1206K
J5: 1.27CONN2; CONN2_1.27
L2: ASPI-4030S-3R3M-T; INDDFN400X400X300-2
SJ1: SJ
U3: TPS561208DDCR; SOT95P280X110-6

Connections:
3.3V: SJ1.2; also elsewhere on the board
BAT_POS: C30.1, J5.P$2 (2), U3.3 (VIN), U3.5 (EN)
unnamed: C32.1, C34.1, L2.2, SJ1.1
unnamed: C31.2, U3.6 (VBST)
unnamed: C31.1, L2.1, U3.2 (SW)
unnamed: C32.2, C33.1, U3.4 (VFB)
PWGND: C30.2, C33.2, C34.2, J5.P$1 (1), U3.1 (GND); also elsewhere on the board

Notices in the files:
parts and their libraries:
SparkFun-Retired: Licensing: Creative Commons ShareAlike 4.0 International - https://creativecommons.org/licenses/by-sa/4.0
